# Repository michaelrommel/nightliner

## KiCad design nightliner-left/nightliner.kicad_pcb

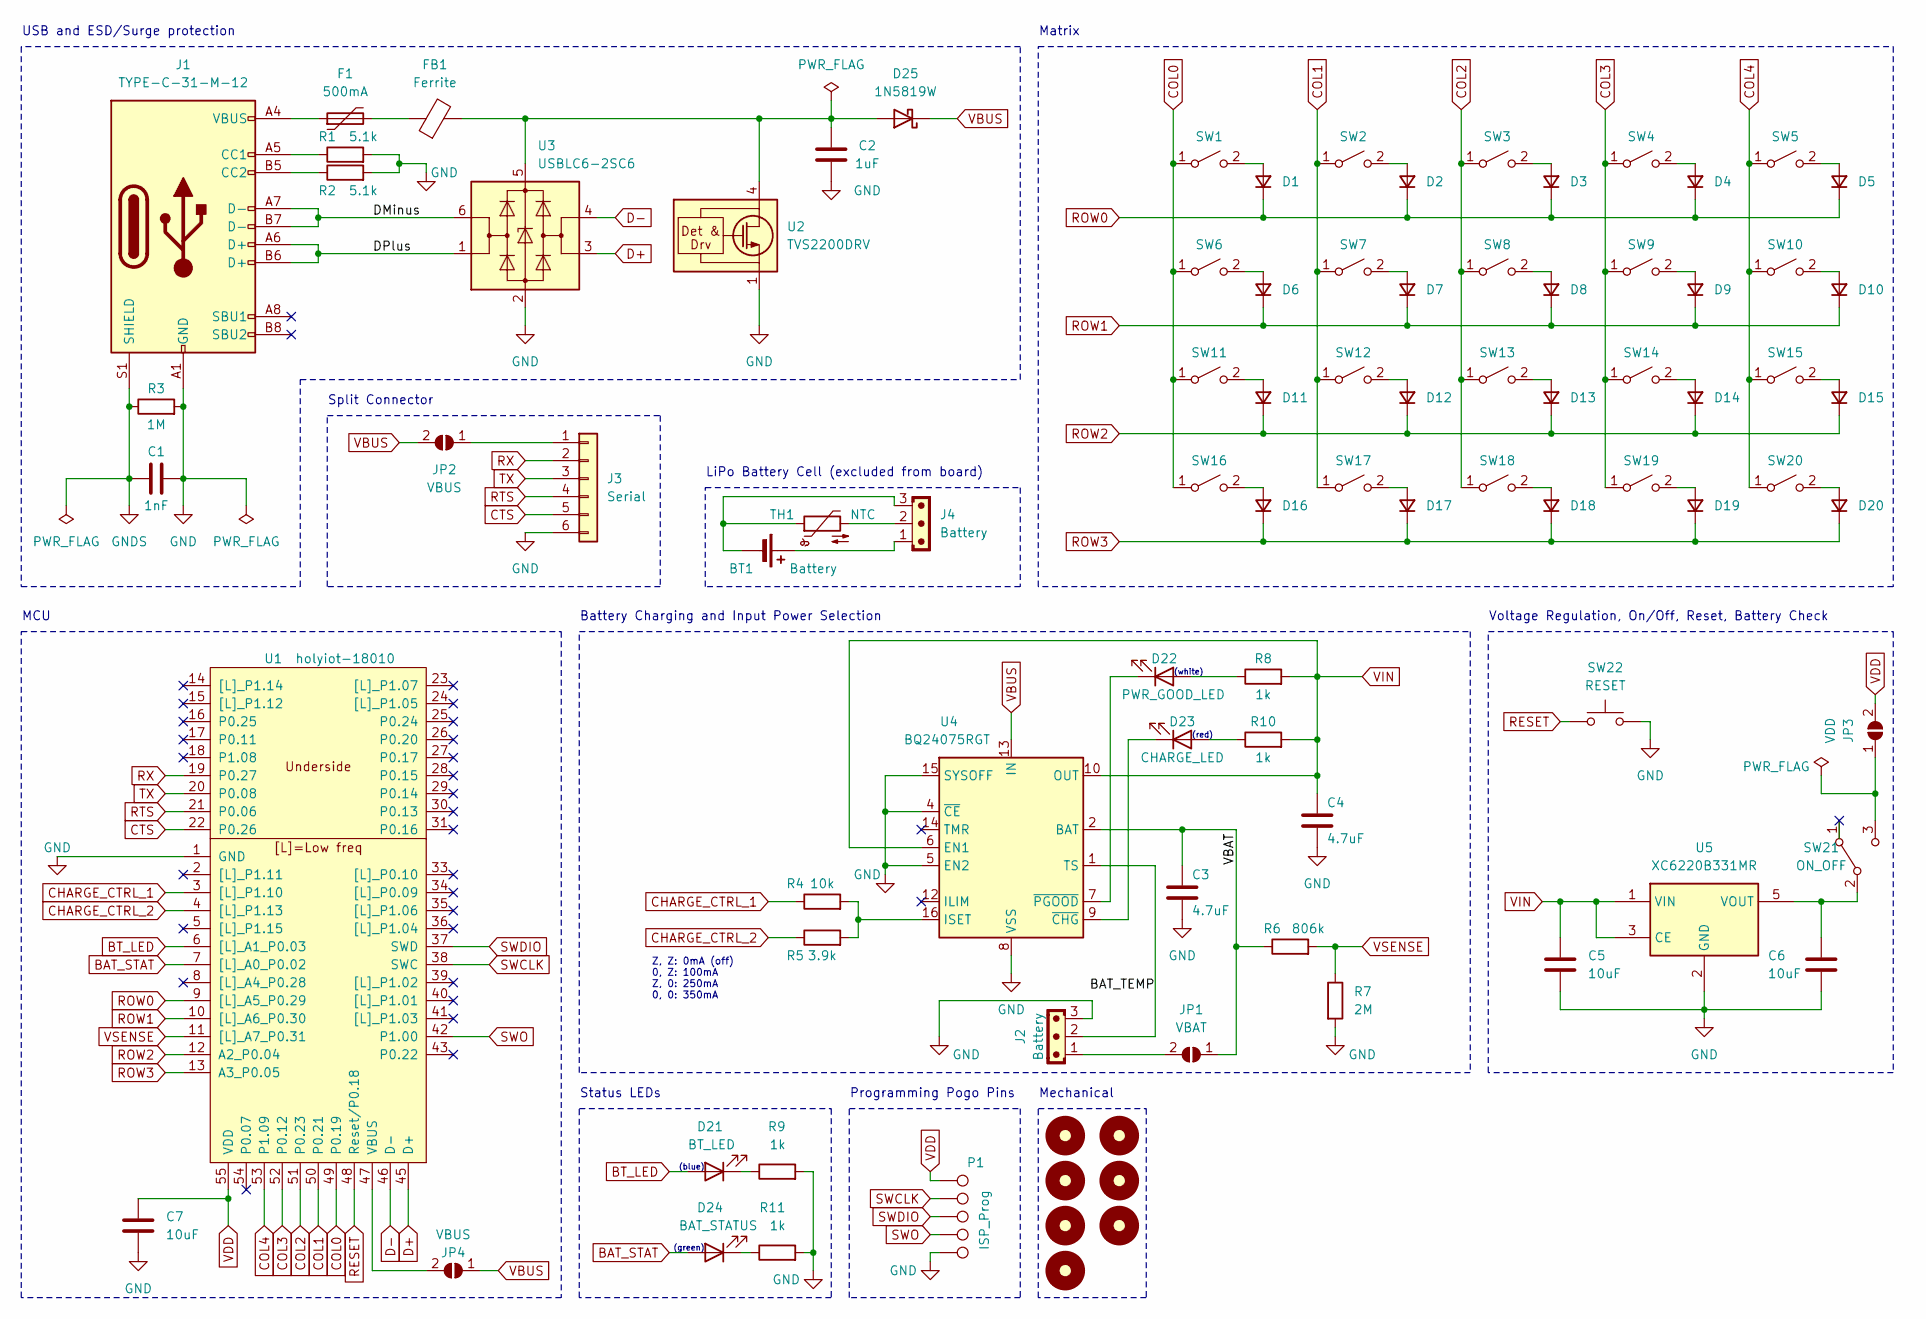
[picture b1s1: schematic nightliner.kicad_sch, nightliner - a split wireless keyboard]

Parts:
BT1: Battery
C1: 1nF; C_0805_2012Metric
C2: 1uF; C_0805_2012Metric
C3, C4: 4.7uF; C_0805_2012Metric
C5, C6, C7: 10uF; C_0805_2012Metric
D1, D2, D3, D4, D5, D6, D7, D8, D9, D10, D11, D12, D13, D14, D15, D16, D17, D18, D19, D20: D_Small; D_SOD-323
D21: BT_LED; LED_0603_1608Metric; PartNumber LTST-C194TBKT; LCSCNumber C575417
D22: PWR_GOOD_LED; LED_0603_1608Metric; PartNumber LTW-C194TS5; LCSCNumber C575432
D23: CHARGE_LED; LED_0603_1608Metric; PartNumber LTST-C194KRKT; LCSCNumber C913101
D24: BAT_STATUS; LED_0603_1608Metric; PartNumber LTST-C194KGKT; LCSCNumber C913102
D25: 1N5819W; D_SOD-123
F1: 500mA; Fuse_0603_1608Metric; PartNumber BSMD0603-050-6V; LCSCNumber C883095
FB1: Ferrite; C_0603_1608Metric; PartNumber BLM18PG121SN1D; LCSCNumber C14709
H1: Standoff_6mm_M3; StandOff_6mm_M3
H2, H3, H4, H5, H6, H7: MountingHole_M3; StandOff_6mm_M3
J1: TYPE-C-31-M-12; PartNumber TYPE-C-31-M-12; LCSCNumber C165948
J2: Battery; JST_XH_S3B-XH-A-1_1x03_P2.50mm_Horizontal
J3: Serial; MagConn_6pin_left
J4: Battery; JST_EH_B3B-EH-A_1x03_P2.50mm_Vertical
JP1: VBAT; SolderJumper-2_P1.3mm_Open_RoundedPad1.0x1.5mm
JP2, JP4: VBUS; SolderJumper-2_P1.3mm_Open_RoundedPad1.0x1.5mm
JP3: VDD; SolderJumper-2_P1.3mm_Open_RoundedPad1.0x1.5mm
P1: ISP_Prog; ISP_Programming_Pads
R1, R2: 5.1k; R_0805_2012Metric
R3: 1M; R_0805_2012Metric
R4: 10k; R_0805_2012Metric
R5: 3.9k; R_0805_2012Metric
R6: 806k; R_0805_2012Metric
R7: 2M; R_0805_2012Metric
R8, R9, R10, R11: 1k; R_0805_2012Metric
SW1: pinky_top; Kailh_Choc_CPG135001D02_Hotswap
SW2: ring_top; Kailh_Choc_CPG135001D02_Hotswap
SW3: middle_top; Kailh_Choc_CPG135001D02_Hotswap
SW4: index_top; Kailh_Choc_CPG135001D02_Hotswap
SW5: inner_top; Kailh_Choc_CPG135001D02_Hotswap
SW6: pinky_home; Kailh_Choc_CPG135001D02_Hotswap
SW7: ring_home; Kailh_Choc_CPG135001D02_Hotswap
SW8: middle_home; Kailh_Choc_CPG135001D02_Hotswap
SW9: index_home; Kailh_Choc_CPG135001D02_Hotswap
SW10: inner_home; Kailh_Choc_CPG135001D02_Hotswap
SW11: pinky_bottom; Kailh_Choc_CPG135001D02_Hotswap
SW12: ring_bottom; Kailh_Choc_CPG135001D02_Hotswap
SW13: middle_bottom; Kailh_Choc_CPG135001D02_Hotswap
SW14: index_bottom; Kailh_Choc_CPG135001D02_Hotswap
SW15: inner_bottom; Kailh_Choc_CPG135001D02_Hotswap
SW16: outer_top; Kailh_Choc_CPG135001D02_Hotswap
SW17: outer_home; Kailh_Choc_CPG135001D02_Hotswap
SW18: near_thumb; Kailh_Choc_CPG135001D02_Hotswap
SW19: home_thumb; Kailh_Choc_CPG135001D02_Hotswap
SW20: far_thumb; Kailh_Choc_CPG135001D02_Hotswap
SW21: ON_OFF; SW_ROCPU_SK-12D07-5_SPDT_Angled
SW22: RESET; SW_Push_1P1T_NO_CK_KSC4xxJ
TH1: NTC
U1: holyiot-18010; HOLYIOT-18010-UndersidePins-SMD
U2: TVS2200DRV; WSON-6-1EP_2x2mm_P0.65mm_EP1x1.6mm
U3: USBLC6-2SC6; SOT-23-6
U4: BQ24075RGT; VQFN-16-1EP_3x3mm_P0.5mm_EP1.6x1.6mm_ThermalVias
U5: XC6220B331MR; SOT-23-5

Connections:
/BAT_TEMP: J2.2, U4.1 (TS)
/DMinus: J1.A7 (D-), J1.B7 (D-), U3.6 (I/O1)
/DPlus: J1.A6 (D+), J1.B6 (D+), U3.1 (I/O1)
/VBAT: C3.1, JP1.1 (A), R6.1, U4.2 (BAT), U4.3 (BAT)
BAT_STAT: D24.2 (A), U1.7 ([L]_A0_P0.02)
BT_LED: D21.2 (A), U1.6 ([L]_A1_P0.03)
CHARGE_CTRL_1: R4.1, U1.3 ([L]_P1.10)
CHARGE_CTRL_2: R5.1, U1.4 ([L]_P1.13)
COL0: SW1.1 (A), SW6.1 (A), SW11.1 (A), SW16.1 (A), U1.49 (P0.19)
COL1: SW2.1 (A), SW7.1 (A), SW12.1 (A), SW17.1 (A), U1.50 (P0.21)
COL2: SW3.1 (A), SW8.1 (A), SW13.1 (A), SW18.1 (A), U1.51 (P0.23)
COL3: SW4.1 (A), SW9.1 (A), SW14.1 (A), SW19.1 (A), U1.52 (P0.12)
COL4: SW5.1 (A), SW10.1 (A), SW15.1 (A), SW20.1 (A), U1.53 (P1.09)
CTS: J3.5, U1.22 (P0.26)
D+: U1.45 (D+), U3.3 (I/O2)
D-: U1.46 (D-), U3.4 (I/O2)
GND: C1.2, C2.1, C3.2, C4.2, C5.2, C6.2, C7.2, J1.A1 (GND), J1.A12 (GND), J1.B1 (GND), J1.B12 (GND), J2.3, J3.6, P1.5 (GND), R1.2, R2.2, R3.2, R7.2, R9.2, R11.2, SW22.2, U1.1 (GND), U1.32 (GND), U1.44 (GND), U2.1 (GND), U2.2 (GND), U2.3 (GND), U2.7 (GND), U3.2 (GND), U4.4 (~CE), U4.5 (EN2), U4.8 (VSS), U4.15 (SYSOFF), U4.17 (VSS), U5.2 (GND)
GNDS: C1.1, J1.S1 (SHIELD), R3.1
unnamed: BT1.1 (+), J4.1
unnamed: BT1.2 (-), J4.3, TH1.1
unnamed: D1.2 (A), SW1.2 (B)
unnamed: D2.2 (A), SW2.2 (B)
unnamed: D3.2 (A), SW3.2 (B)
unnamed: D4.2 (A), SW4.2 (B)
unnamed: D5.2 (A), SW5.2 (B)
unnamed: D6.2 (A), SW6.2 (B)
unnamed: D7.2 (A), SW7.2 (B)
unnamed: D8.2 (A), SW8.2 (B)
unnamed: D9.2 (A), SW9.2 (B)
unnamed: D10.2 (A), SW10.2 (B)
unnamed: D11.2 (A), SW11.2 (B)
unnamed: D12.2 (A), SW12.2 (B)
unnamed: D13.2 (A), SW13.2 (B)
unnamed: D14.2 (A), SW14.2 (B)
unnamed: D15.2 (A), SW15.2 (B)
unnamed: D16.2 (A), SW16.2 (B)
unnamed: D17.2 (A), SW17.2 (B)
unnamed: D18.2 (A), SW18.2 (B)
unnamed: D19.2 (A), SW19.2 (B)
unnamed: D20.2 (A), SW20.2 (B)
unnamed: D21.1 (K), R9.1
unnamed: D22.2 (A), R8.1
unnamed: D22.1 (K), U4.7 (~PGOOD)
unnamed: D23.2 (A), R10.1
unnamed: D23.1 (K), U4.9 (~CHG)
unnamed: D24.1 (K), R11.1
unnamed: C2.2, D25.2 (A), FB1.2, U2.4 (IN), U2.5 (IN), U2.6 (IN), U3.5 (VBUS)
unnamed: F1.1, J1.A4 (VBUS), J1.A9 (VBUS), J1.B4 (VBUS), J1.B9 (VBUS)
unnamed: F1.2, FB1.1
unnamed: J1.A5 (CC1), R1.1
unnamed: J1.B5 (CC2), R2.1
unnamed: J3.1, JP2.1 (A)
unnamed: J4.2, TH1.2
unnamed: J2.1, JP1.2 (B)
unnamed: JP3.1 (A), SW21.3 (C)
unnamed: JP4.2 (B), U1.47 (VBUS)
unnamed: C6.1, SW21.2 (B), U5.5 (VOUT)
unnamed: R4.2, R5.2, U4.16 (ISET)
RESET: SW22.1, U1.48 (Reset/P0.18)
ROW0: D1.1 (K), D2.1 (K), D3.1 (K), D4.1 (K), D5.1 (K), U1.9 ([L]_A5_P0.29)
ROW1: D6.1 (K), D7.1 (K), D8.1 (K), D9.1 (K), D10.1 (K), U1.10 ([L]_A6_P0.30)
ROW2: D11.1 (K), D12.1 (K), D13.1 (K), D14.1 (K), D15.1 (K), U1.12 (A2_P0.04)
ROW3: D16.1 (K), D17.1 (K), D18.1 (K), D19.1 (K), D20.1 (K), U1.13 (A3_P0.05)
RTS: J3.4, U1.21 (P0.06)
RX: J3.2, U1.19 (P0.27)
SWCLK: P1.2 (SWCLK), U1.38 (SWC)
SWDIO: P1.3 (SWDIO), U1.37 (SWD)
SWO: P1.4 (SWO), U1.42 (P1.00)
TX: J3.3, U1.20 (P0.08)
VBUS: D25.1 (K), JP2.2 (B), JP4.1 (A), U4.13 (IN)
VDD: C7.1, JP3.2 (B), P1.1 (VDD), U1.55 (VDD)
VIN: C4.1, C5.1, R8.2, R10.2, U4.6 (EN1), U4.10 (OUT), U4.11 (OUT), U5.1 (VIN), U5.3 (CE)
VSENSE: R6.2, R7.1, U1.11 ([L]_A7_P0.31)

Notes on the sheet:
Programming Pogo Pins
Mechanical
Battery Charging and Input Power Selection
Status LEDs
Voltage Regulation, On/Off, Reset, Battery Check
Split Connector
MCU
(red)
Z, Z: 0mA (off) 0, Z: 100mA Z, 0: 250mA 0, 0: 350mA
Matrix
(green)
(white)
LiPo Battery Cell (excluded from board)
(blue)
USB and ESD/Surge protection

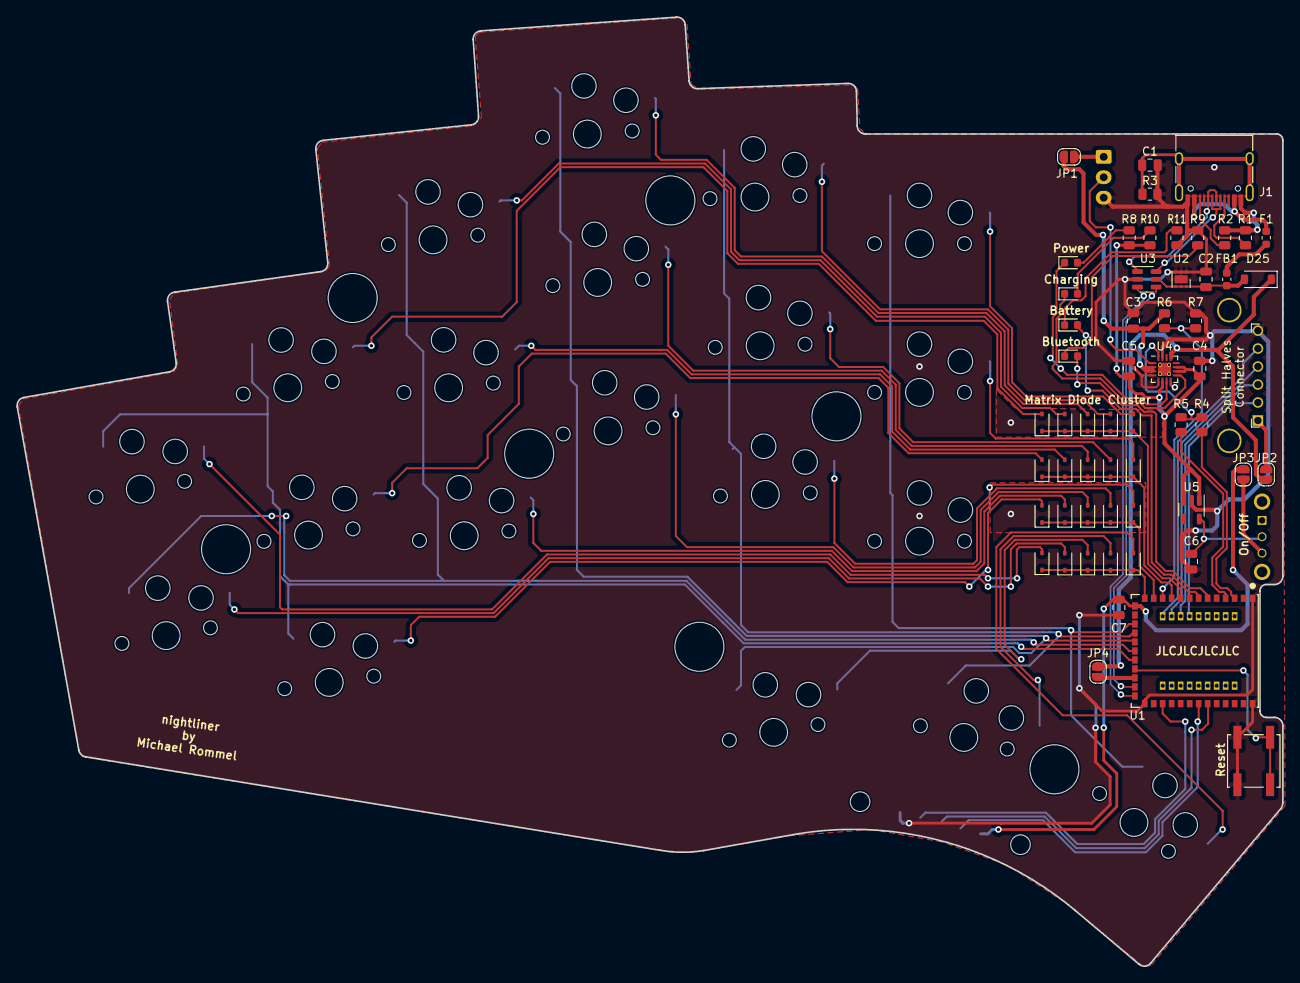
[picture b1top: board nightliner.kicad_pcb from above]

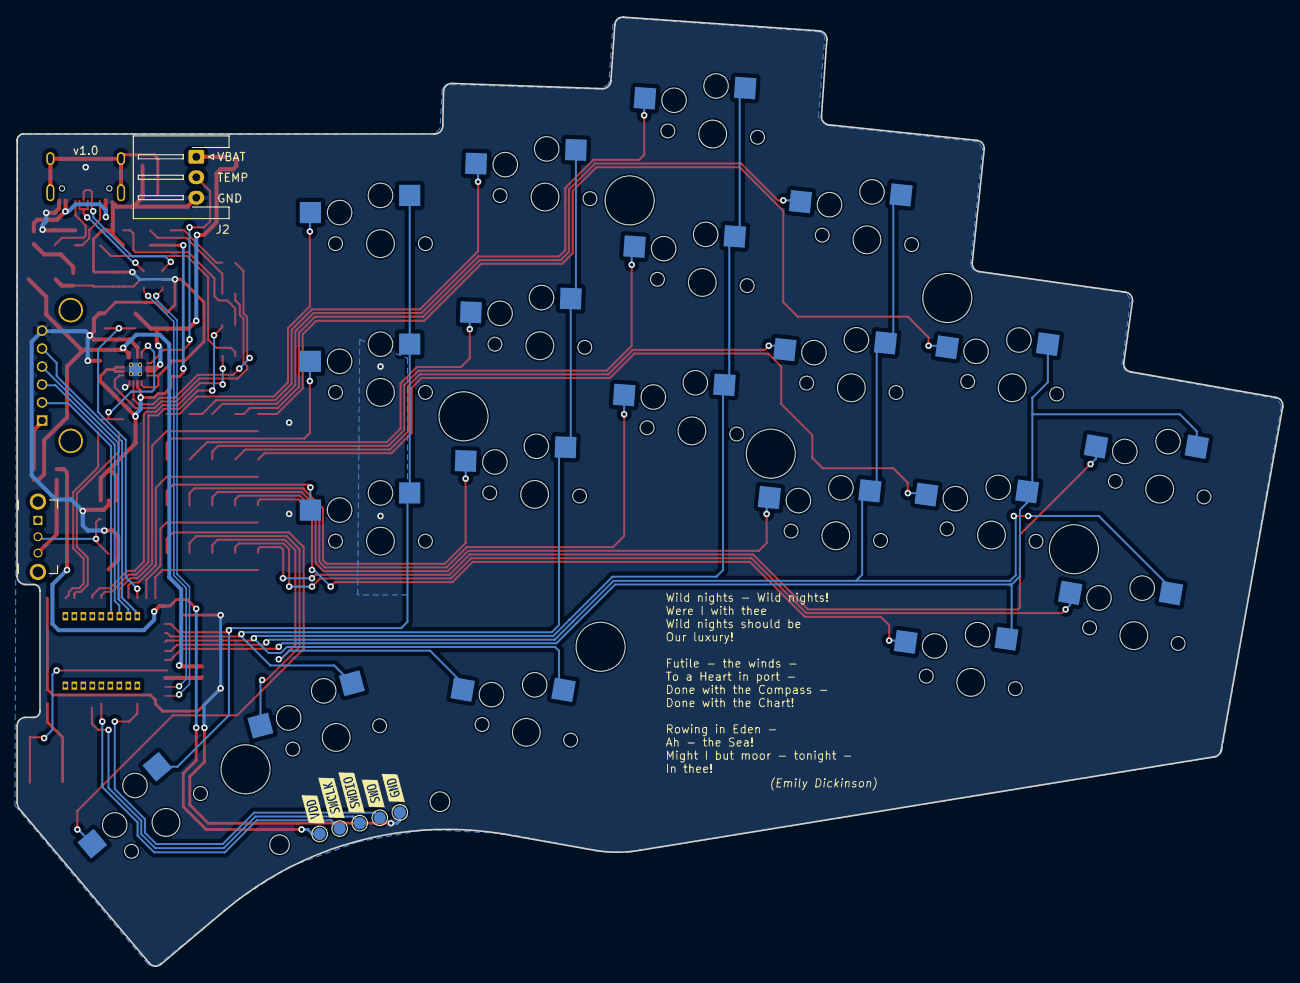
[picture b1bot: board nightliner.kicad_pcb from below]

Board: 2 copper layers, 154.8 x 116.1 mm, 87 parts (3 on the bottom side), 70 nets.

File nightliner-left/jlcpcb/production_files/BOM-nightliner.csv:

Comment,Designator,Footprint,LCSC
Ferrite,FB1,C_0603_1608Metric,C14709
TYPE-C-31-M-12,J1,USB_C_Receptacle_HRO_TYPE-C-31-M-12,C165948
BT_LED,D21,LED_0603_1608Metric,C575417
PWR_GOOD_LED,D22,LED_0603_1608Metric,C575432
500mA,F1,Fuse_0603_1608Metric,C883095
CHARGE_LED,D23,LED_0603_1608Metric,C913101
BAT_STATUS,D24,LED_0603_1608Metric,C913102
VBAT,JP1,SolderJumper-2_P1.3mm_Open_RoundedPad1.0x1.5mm,
D_Small,D11,D_SOD-323,
806k,R6,R_0805_2012Metric,
D_Small,D17,D_SOD-323,
1k,R8,R_0805_2012Metric,
pinky_home,SW6,Kailh_Choc_CPG135001D02_Hotswap,
MountingHole_M3,H2,StandOff_6mm_M3,
ring_top,SW2,Kailh_Choc_CPG135001D02_Hotswap,
D_Small,D15,D_SOD-323,
D_Small,D20,D_SOD-323,
D_Small,D16,D_SOD-323,
4.7uF,C4,C_0805_2012Metric,
1nF,C1,C_0805_2012Metric,
holyiot-18010,U1,HOLYIOT-18010-UndersidePins-SMD,
D_Small,D5,D_SOD-323,
middle_top,SW3,Kailh_Choc_CPG135001D02_Hotswap,
TVS2200DRV,U2,WSON-6-1EP_2x2mm_P0.65mm_EP1x1.6mm,
RESET,SW22,SW_Push_1P1T_NO_CK_KSC4xxJ,
outer_top,SW16,Kailh_Choc_CPG135001D02_Hotswap,
MountingHole_M3,H5,StandOff_6mm_M3,
1k,R11,R_0805_2012Metric,
VBUS,JP4,SolderJumper-2_P1.3mm_Open_RoundedPad1.0x1.5mm,
far_thumb,SW20,Kailh_Choc_CPG135001D02_Hotswap,
10k,R4,R_0805_2012Metric,
inner_top,SW5,Kailh_Choc_CPG135001D02_Hotswap,
home_thumb,SW19,Kailh_Choc_CPG135001D02_Hotswap,
1k,R10,R_0805_2012Metric,
inner_home,SW10,Kailh_Choc_CPG135001D02_Hotswap,
10uF,C5,C_0805_2012Metric,
D_Small,D18,D_SOD-323,
ring_bottom,SW12,Kailh_Choc_CPG135001D02_Hotswap,
Serial,J3,MagConn_6pin_left,
D_Small,D2,D_SOD-323,
D_Small,D7,D_SOD-323,
1M,R3,R_0805_2012Metric,
1N5819W,D25,D_SOD-123,
index_home,SW9,Kailh_Choc_CPG135001D02_Hotswap,
D_Small,D19,D_SOD-323,
D_Small,D6,D_SOD-323,
3.9k,R5,R_0805_2012Metric,
pinky_top,SW1,Kailh_Choc_CPG135001D02_Hotswap,
2M,R7,R_0805_2012Metric,
5.1k,R1,R_0805_2012Metric,
inner_bottom,SW15,Kailh_Choc_CPG135001D02_Hotswap,
XC6220B331MR,U5,SOT-23-5,
D_Small,D1,D_SOD-323,
MountingHole_M3,H3,StandOff_6mm_M3,
1k,R9,R_0805_2012Metric,
D_Small,D3,D_SOD-323,
MountingHole_M3,H7,StandOff_6mm_M3,
USBLC6-2SC6,U3,SOT-23-6,
middle_home,SW8,Kailh_Choc_CPG135001D02_Hotswap,
pinky_bottom,SW11,Kailh_Choc_CPG135001D02_Hotswap,
index_top,SW4,Kailh_Choc_CPG135001D02_Hotswap,
MountingHole_M3,H6,StandOff_6mm_M3,
D_Small,D4,D_SOD-323,
VBUS,JP2,SolderJumper-2_P1.3mm_Open_RoundedPad1.0x1.5mm,
D_Small,D14,D_SOD-323,
middle_bottom,SW13,Kailh_Choc_CPG135001D02_Hotswap,
outer_home,SW17,Kailh_Choc_CPG135001D02_Hotswap,
ring_home,SW7,Kailh_Choc_CPG135001D02_Hotswap,
10uF,C7,C_0805_2012Metric,
1uF,C2,C_0805_2012Metric,
index_bottom,SW14,Kailh_Choc_CPG135001D02_Hotswap,
MountingHole_M3,H4,StandOff_6mm_M3,
10uF,C6,C_0805_2012Metric,
D_Small,D9,D_SOD-323,
D_Small,D8,D_SOD-323,
D_Small,D10,D_SOD-323,
D_Small,D13,D_SOD-323,
Standoff_6mm_M3,H1,StandOff_6mm_M3,
4.7uF,C3,C_0805_2012Metric,
near_thumb,SW18,Kailh_Choc_CPG135001D02_Hotswap,
VDD,JP3,SolderJumper-2_P1.3mm_Open_RoundedPad1.0x1.5mm,
D_Small,D12,D_SOD-323,
5.1k,R2,R_0805_2012Metric,
BQ24075RGT,U4,VQFN-16-1EP_3x3mm_P0.5mm_EP1.6x1.6mm_ThermalVias,
Battery,J2,JST_XH_S3B-XH-A-1_1x03_P2.50mm_Horizontal,
ISP_Prog,P1,ISP_Programming_Pads,
ON_OFF,SW21,SW_ROCPU_SK-12D07-5_SPDT_Angled,

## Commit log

2023-10-23 feat: first version of schematics
2023-10-23 feat: schematics with partial footprints
2023-10-23 feat: first PCB placement
2023-10-25 feat: PCB placement (with wrong choc pos)
2023-10-25 feat: routed PCB, ready for fills
2023-10-26 fix: DRC errors, updated footprints
2023-10-26 feat: add mounting holes, better labels
2023-10-26 feat: change connector and on/off switch, re-layout
2023-10-28 fix: footprint for prog header, mounting holes, drc check
2023-10-30 feat: move all outlines to KiCAD, update footprints
2023-10-31 feat: case for the keyboard
2023-10-31 fix: move battery connector to top
2023-11-01 fix: add 0.2mm offset for case clearance
2023-11-02 feat: add split pogo connector, reroute board
2023-11-02 fix: move mag connector up, preserve wall thickness of case
2023-11-04 feat: create right side pcb, clean up footprints
2023-11-06 fix: make sides symmetric
2023-11-07 feat: initial right side case completed
2023-11-09 fix: change edge outline, flip switches
2023-11-14 feat: outline change, fix right pinky column
2023-11-23 fix: rework right case, fix outline
2023-12-03 fix: final version, create production gerbers
